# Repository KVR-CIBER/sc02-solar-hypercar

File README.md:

# SC-02 · Solar Hypercar

**Een gesloten Le-Mans-hypercar op zonne-energie, op schaal, voor de Solar Olympiade.**
De wagen is volledig 3D-printbaar (PLA + TPU-banden). Hij heeft een Raspberry Pi 4 en een ESP32-S3 aan boord, je bestuurt hem met een Bluetooth-controller of met je gsm, en alles is eerst in een fysica-simulatie getest voordat er één gram plastic geprint werd.

### ▶ [Website met films en beelden](https://kvr-ciber.github.io/sc02-solar-hypercar/) · 🏎 [Rij zelf in de simulatie](https://kvr-ciber.github.io/sc02-solar-hypercar/sim/) · 🔧 [3D-assemblage](https://kvr-ciber.github.io/sc02-solar-hypercar/sim/build.html)

|  |  |  |
|:---:|:---:|:---:|
| ▶ Rondje op het circuit | ▶ Assemblage | ▶ SC-01 Challenger |

## Specificaties

| | |
|---|---|
| Gewicht | ± 715 g (met 3S LiPo en Pi 4) |
| Batterij | 3S LiPo 1300 mAh (11,1 V) |
| Elektronica | Raspberry Pi 4 (brug naar controller/gsm) + ESP32-S3 (realtime aansturing) |
| Motordrivers | 2× DRV8871 (vooruit, achteruit, remmen) |
| Motoren | 2× Tamiya Hyper-Dash / Mach-Dash, of goedkope 130-motoren |
| Overbrenging | tandwielen module 0,8, 10:35. Printbaar, of CNC-gefreesd in POM |
| Zonnepaneel | 1 W, 110 × 60 mm, dwars op het dek |
| Banden | geprint in TPU 95A, klikken op de velg zoals een fietsband |
| Topsnelheid (simulatie) | ± 45 km/h met de Tamiya-motoren |

## Wat zit waar

| Map | Inhoud |
|---|---|
| [`f1/cad/`](f1/cad/) | Parametrische CadQuery-CAD: `p.py` (alle maten), `body.py` (carrosserie), `car.py` (alle onderdelen), `gears.py` (tandwielen), `build.py` (STL, STEP, DXF, GLB + controles) |
| [`f1/firmware/sc02/`](f1/firmware/sc02/) | ESP32-S3-firmware: motoren, stuurservo, tractiecontrole, failsafe, launch |
| [`f1/pi/`](f1/pi/) | Raspberry Pi 4: Bluetooth-controller + gsm-besturing via hotspot (`sc02_pi.py`, `phone.html`, systemd-service) |
| [`f1/web/`](f1/web/) | De 3D-simulatie in de browser (three.js) |
| [`PRINTEN_PLA_TPU/`](PRINTEN_PLA_TPU/) | **Alles printklaar**, al in de juiste printstand, met instructies |
| [`site/`](site/) | De projectwebsite (GitHub Pages), samengesteld door `site/build_site.sh` |
| [`video/`](video/) | Films in 1080p |
| [`docs/`](docs/) | Bedrading, stuklijst, ontwerpverslag, motormetingen, en het [README van de eerste versie (SC-01)](docs/SC-01_README.md) |
| `sim/`, `cad/`, `firmware/`, `pit/` | De eerste wagen SC-01 (Challenger-klasse) |

## Printen

Alles in **PLA**, alleen de **banden in TPU 95A**. Elk bestand staat al in de juiste printstand, en het getal vooraan de bestandsnaam (`2x_…`) zegt hoeveel je er nodig hebt.
De volledige instellingen per onderdeel staan in [`PRINTEN_PLA_TPU/LEESMIJ.md`](PRINTEN_PLA_TPU/LEESMIJ.md).

Kort:
- Carrosserie: 0,2 mm, tree supports, 3 wanden, 12 % infill.
- Velgen en tandwielen: 0,12 mm, 3 wanden, 25 % infill.
- Motorwieg en motorklem: liever 100 % infill, want de motoren worden warm.
- Banden: TPU, langzaam (± 25 mm/s), geen supports.

## Simulatie

Online speelbaar op **https://kvr-ciber.github.io/sc02-solar-hypercar/sim/** (WASD of pijltjes, spatie = rem, C = camera, R = reset, gamepad werkt ook). In de instellingen kies je tussen het **circuit** en een **oneindige rechte lijn** met afstandsteller en 12 m-sprinttimer. Met de knop **direct / BT · 35 ms / gsm · 120 ms** voel je de vertraging (met schommeling) die je zou hebben als je de echte wagen via de Pi bestuurt: Bluetooth-controller → Pi 4 → UART → ESP32, of gsm via de hotspot. Dat zijn schattingen, nog niet gemeten op de echte wagen.

Lokaal draaien:

```bash
cd f1/web
python3 -m http.server 8000
# open http://localhost:8000
```

## Hoe we het gemaakt hebben

1. **Reglement eerst.** We begonnen met het reglement van de Solar Olympiade: maximale breedte, verplicht zonnepaneel met diode, batterijregels. Elke ontwerpkeuze moest daar binnen passen.

2. **Fysica-simulatie (SC-01).** Voor de eerste wagen schreven we een race-simulatie met batterij, motor, bandslip en launch control. Daarmee kozen we motor, overbrenging en wielmaat. Resultaat: **2,33 s over 12 m** vanuit stilstand. Zie [docs/SC-01_README.md](docs/SC-01_README.md).

3. **Parametrische CAD.** Het hele model is code (CadQuery). Eén maat aanpassen in `p.py`, `build.py` draaien, en alle STL-, STEP- en DXF-bestanden worden opnieuw gemaakt.

4. **"Te speelgoed."** De eerste versie werkte, maar zag eruit als speelgoed: open wielen, zichtbare draden en schroeven. Dat was de belangrijkste feedback.

5. **SC-02: gesloten Le-Mans-hypercar.** Daarom een volledig nieuw ontwerp: wielen in wielkasten, een gesloten carrosserie, een koepel, achtervleugel, splitter en diffuser. Van buiten zie je niets van de techniek.

6. **CAD-problemen opgelost.** Een paar die we onderweg tegenkwamen:
   - **OCC-booleans faalden stil.** Ze gaven een leeg of kapot resultaat zonder foutmelding. Oplossing: de booleans laten doen door `manifold3d`, dat altijd een waterdicht resultaat geeft.
   - **De loft vouwde de staart en de neus terug.** De carrosserie klapte op zichzelf. Oplossing: rechtstreeks OCC `ThruSections` aanroepen, met volledige controle over de doorsneden.
   - **Zwevende magneetbosjes.** De houders voor de magneten van de carrosserie hingen in de lucht, los van de wand. Ze zijn nu verbonden met de structuur.
   - **Botsende onderdelen.** Een volledige botsingscontrole test elk onderdeel tegen elk ander (nu: 0 botsingen). Zo vonden we o.a. een diffuser in de vloer, splitter-vinnen door de vloer, een koepel door het dek, een te korte batterijbak en ESP-pinnen door de Pi-USB.
   - **Twee echte ontwerpfouten.** De carrosserie zat vast op de achteras (gesloten wielkasten): nu zijn de asgleuf en wielkasten onderaan open en tilt de body er gewoon af. En de motoren konden niet in het tandwiel zakken: nu schuiven ze langs hun as van achteren in de wieg.

7. **Firmware en Pi-brug.** De ESP32-S3 doet het realtime werk: tractiecontrole, een failsafe die stopt als het signaal wegvalt, en een launch-modus. De Pi 4 is de brug: hij leest een Bluetooth-controller in, en via een hotspot kun je ook met je gsm sturen.

8. **three.js-simulatie.** Een 3D-simulatie in de browser met een fietsmodel voor het sturen, Pacejka-banden voor de grip, en het verbruik per onderdeel (Pi, ESP, servo, motoren), live tijdens het rijden.

9. **Printplaten en STEP-bestanden.** Alle onderdelen zijn verdeeld over printplaten, in de juiste printstand, en ook beschikbaar als STEP om verder te bewerken in Fusion, FreeCAD of Onshape.

10. **Budget.** We vergeleken AliExpress met Europese leveranciers, inclusief de EU-invoerheffing op kleine pakketjes. Goedkoop bestellen is niet altijd goedkoper.

11. **Assemblage-animatie.** 24 stappen, en elke montagebeweging is nagerekend tegen de CAD (40 punten per baan): geen enkel onderdeel gaat door een ander. Ook [interactief in 3D](https://kvr-ciber.github.io/sc02-solar-hypercar/sim/build.html).

## Niet in deze repo

- Het reglement van de Solar Olympiade (auteursrecht van de organisatie).
- Wachtwoorden: kopieer `firmware/solar_car/secrets.example.h` naar `secrets.h` en vul je eigen hotspotgegevens in.
- 4K-video's (te groot voor GitHub; de 1080p-versies staan erin).

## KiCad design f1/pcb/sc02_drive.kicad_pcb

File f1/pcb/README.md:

# SC-02 drive board (v3.0)

A **compact 86 x 90 mm board on 4x M3 standoffs**, with the 3S LiPo on top of it. No Raspberry Pi anymore, a **built-in
ExpressLRS 2.4 GHz receiver** for the RadioMaster Pocket, and a real **solar-panel connector**.
(v2 was the whole car floor; that is gone: the car floor goes back to the 2 mm acrylic / printed floor.)

| Block | Parts |
|---|---|
| Power (unchanged from v2) | **XT60**, 10 A fuse, power switch pads, P-MOSFET reverse protection, **INA226** + 2 mOhm shunt, **TPS54560B 5 V 5 A** buck |
| Car brain | **ESP32-S3-WROOM-1** (antenna at the bottom edge), USB-C at the edge, RESET / BOOT |
| Motor | **one brushless 2435 4500 KV + 40 A ESC** (11:35). The ESC takes its power straight from the battery (Y-cable on the XT60); this board only sends the throttle signal (**ESC** header, IO4) and reads a 10k NTC on the ESC/motor (**ESC TEMP**, IO5) for the boost limit |
| **ExpressLRS receiver** | **ESP32-C3-MINI-1** + **Ebyte E28-2G4M12S** (SX1280, 12.5 dBm, PCB antenna at the right edge), own 3.3 V LDO, RGB status LED, BIND button |
| Connectors | servo (MG90S), hall (A3144), lights (switched 5 V), **solar panel JST-XH 2-pin**, Qwiic I2C |

Checks: **DRC 0, unconnected 0, ERC 0, schematic parity 0.** JLC BOM/CPL in `fab/` with LCSC numbers.

## ExpressLRS: flashing and binding
The receiver is wired exactly like ExpressLRS' **"Generic C3 2400"** target (SCK 6, MOSI 4, MISO 5, NSS 7, BUSY 3, DIO1 1,
RST 2, LED 8, button 9, CRSF on 20/21), so the normal ExpressLRS firmware runs on it, no custom layout needed.
1. First flash: ExpressLRS Configurator -> target **Generic C3 2400 RX**, flash method **WiFi** or via the **RX USB** pads
   (D-, D+, GND: a cut USB cable) while holding **BIND** at power-on.
2. Bind with the Pocket (binding phrase, or press BIND 3x).
3. CRSF goes to the car ESP32-S3: C3 TX -> **IO16**, S3 **IO15** -> C3 RX (420000 baud). The S3 can reset the receiver
   (**IO17** -> EN) and start its bootloader (**IO18** -> IO9), so later updates can go through the car's USB-C.
Tip: keep the S3's own WiFi off while driving (same 2.4 GHz band).

## Solar panel
JST-XH 2-pin (**-** / **+**), voltage on IO8 (x 4.03). Solder jumper **JP1 (ZON>5V)**, open by default: closed, the panel
helps the 5 V rail through a Schottky diode. Only close it with a panel whose open-circuit voltage is at most 6 V.

## ESP32-S3 pins
| GPIO | | GPIO | |
|---|---|---|---|
| 4 | ESC throttle (servo PWM / DShot) | 5 | ESC/motor NTC (ADC) |
| 9 | servo | 38 | hall |
| 15 / 16 | CRSF TX / RX (receiver) | 17 / 18 | receiver EN / BOOT |
| 1 / 2 | I2C SDA / SCL (INA226 0x40 + Qwiic) | 8 | solar panel voltage |
| 11 | lights | 12 | yellow LED |

## Still to do
* Car CAD: floor back to acrylic + 4 standoff holes for this board, battery tray on top, USB-C opening at the new place.
* Firmware `car.cpp`: ESC on IO4 (with arming), CRSF on IO15/16, boost on CH5 with the NTC temperature limit, hall IO38.
* ESC wiring: XT60 Y-cable battery -> ESC + this board; do NOT connect the ESC's red BEC wire to the board.

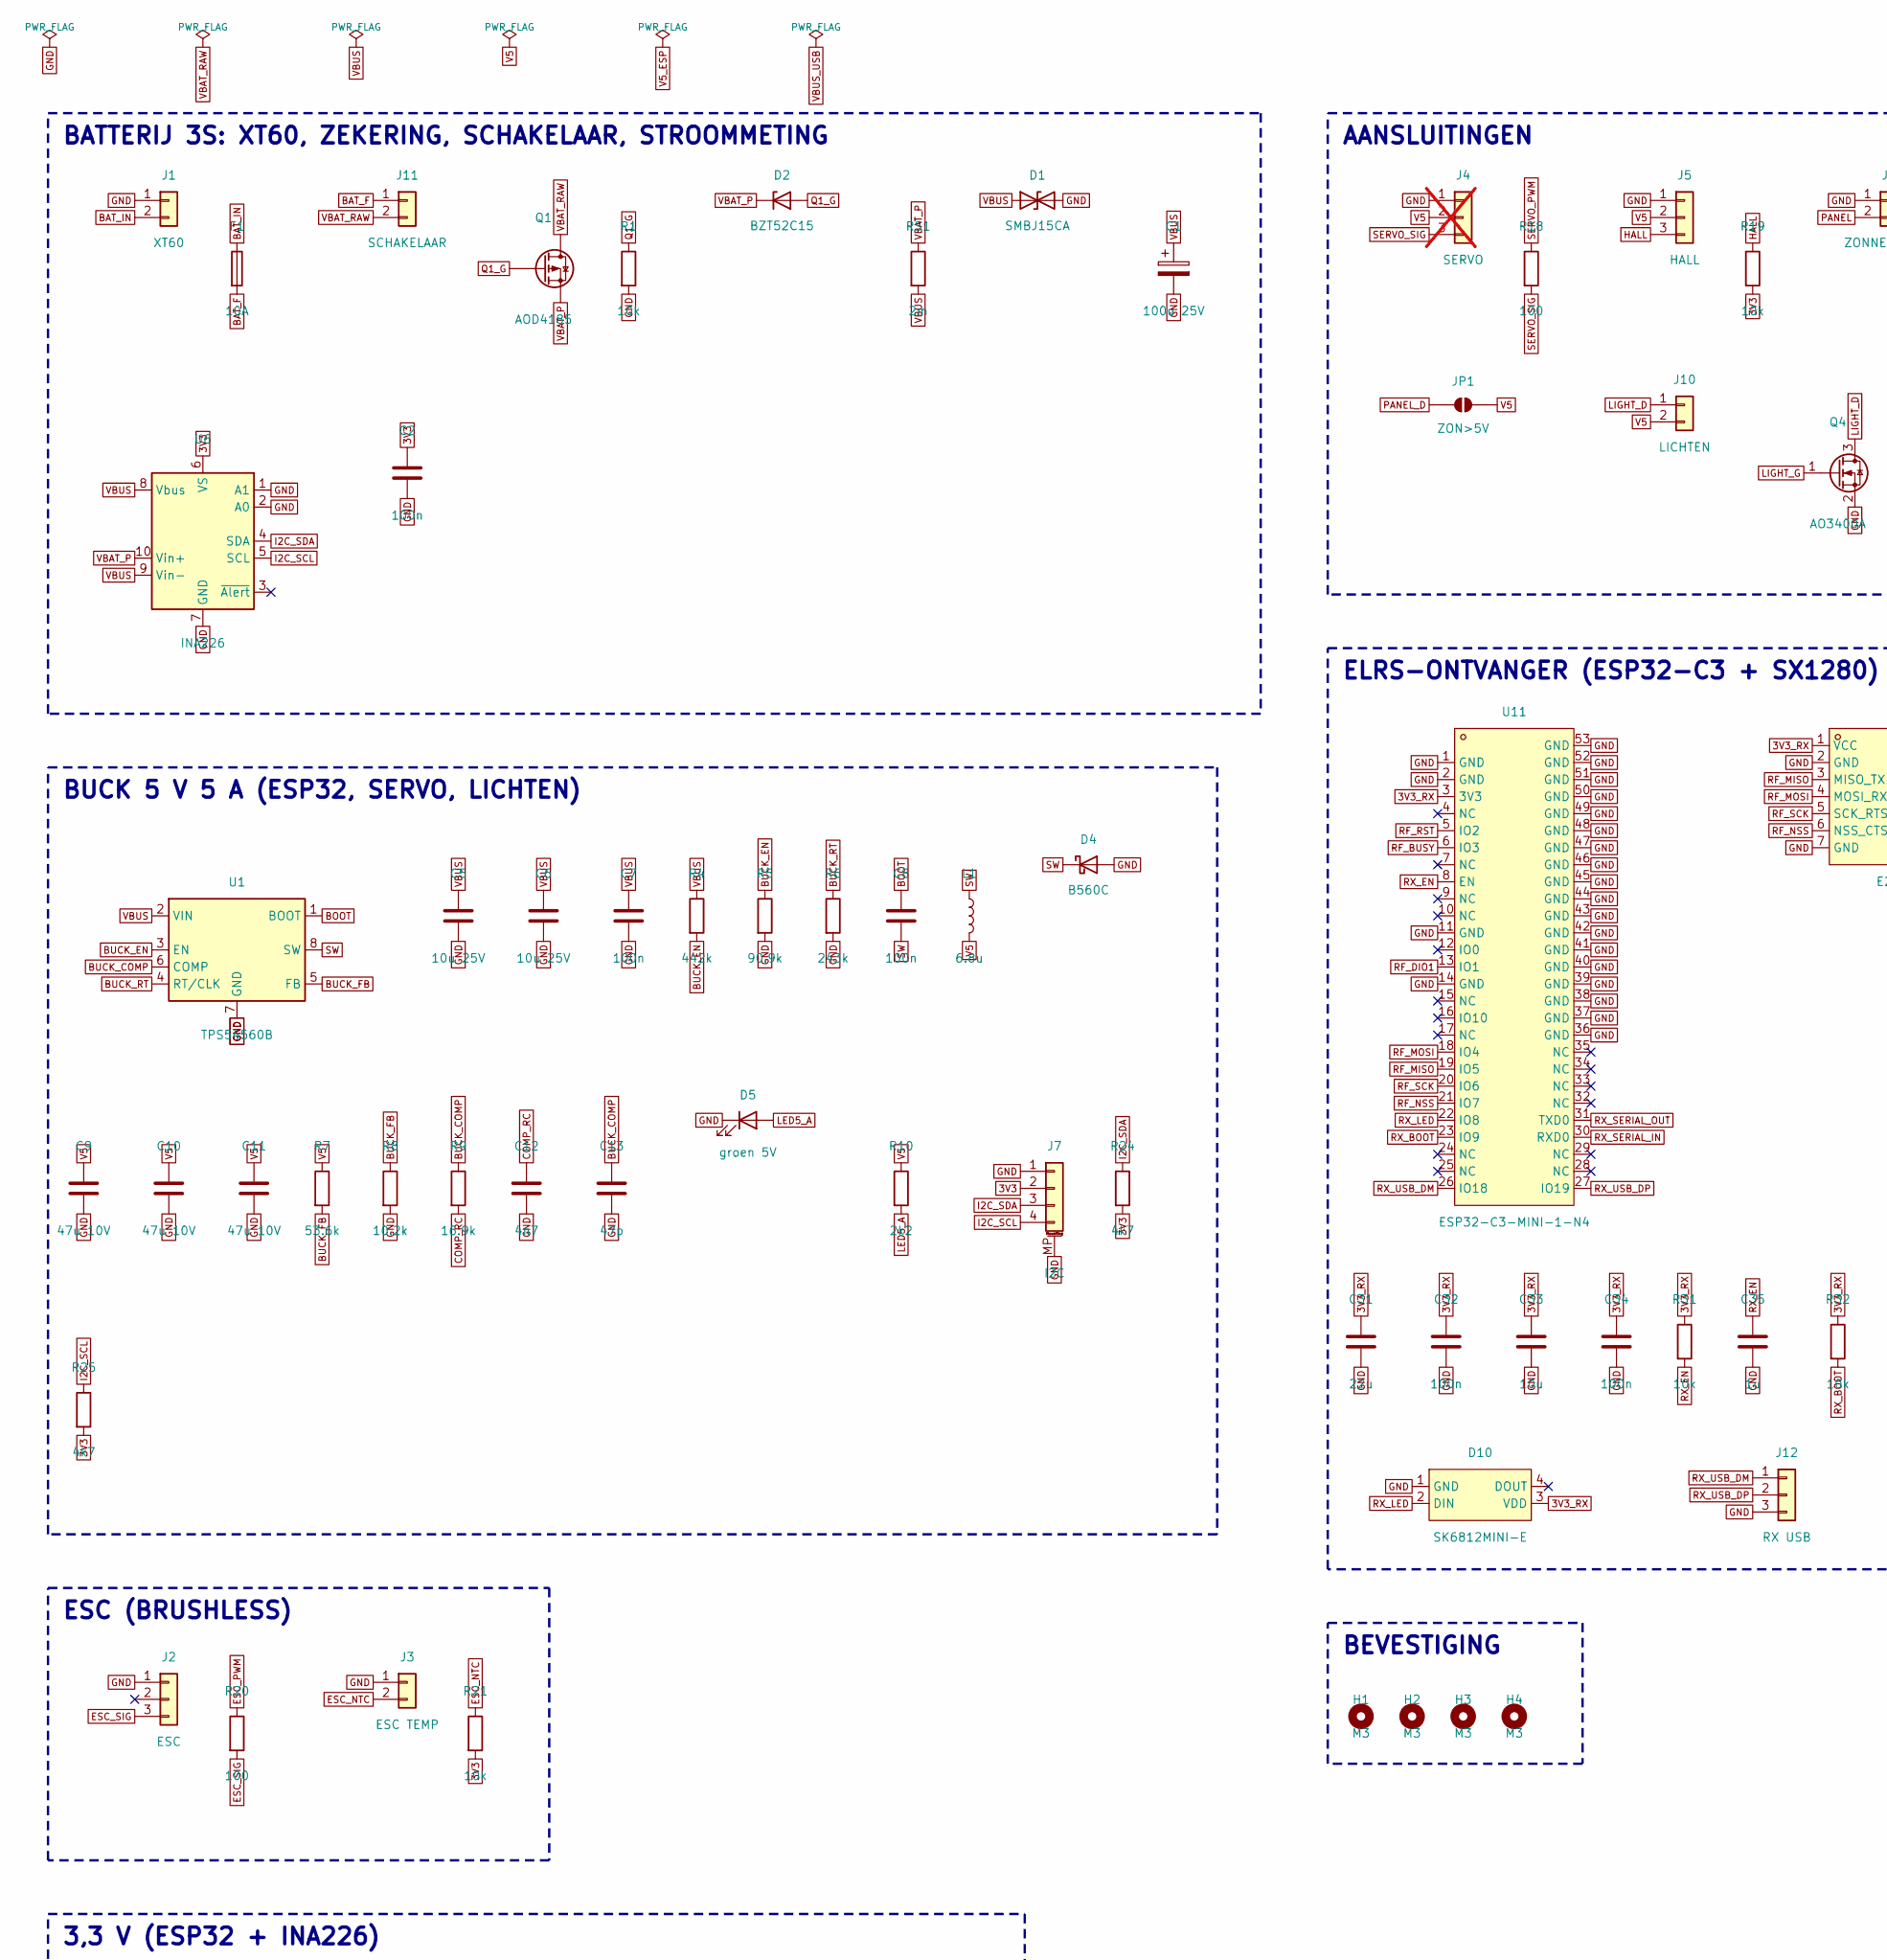
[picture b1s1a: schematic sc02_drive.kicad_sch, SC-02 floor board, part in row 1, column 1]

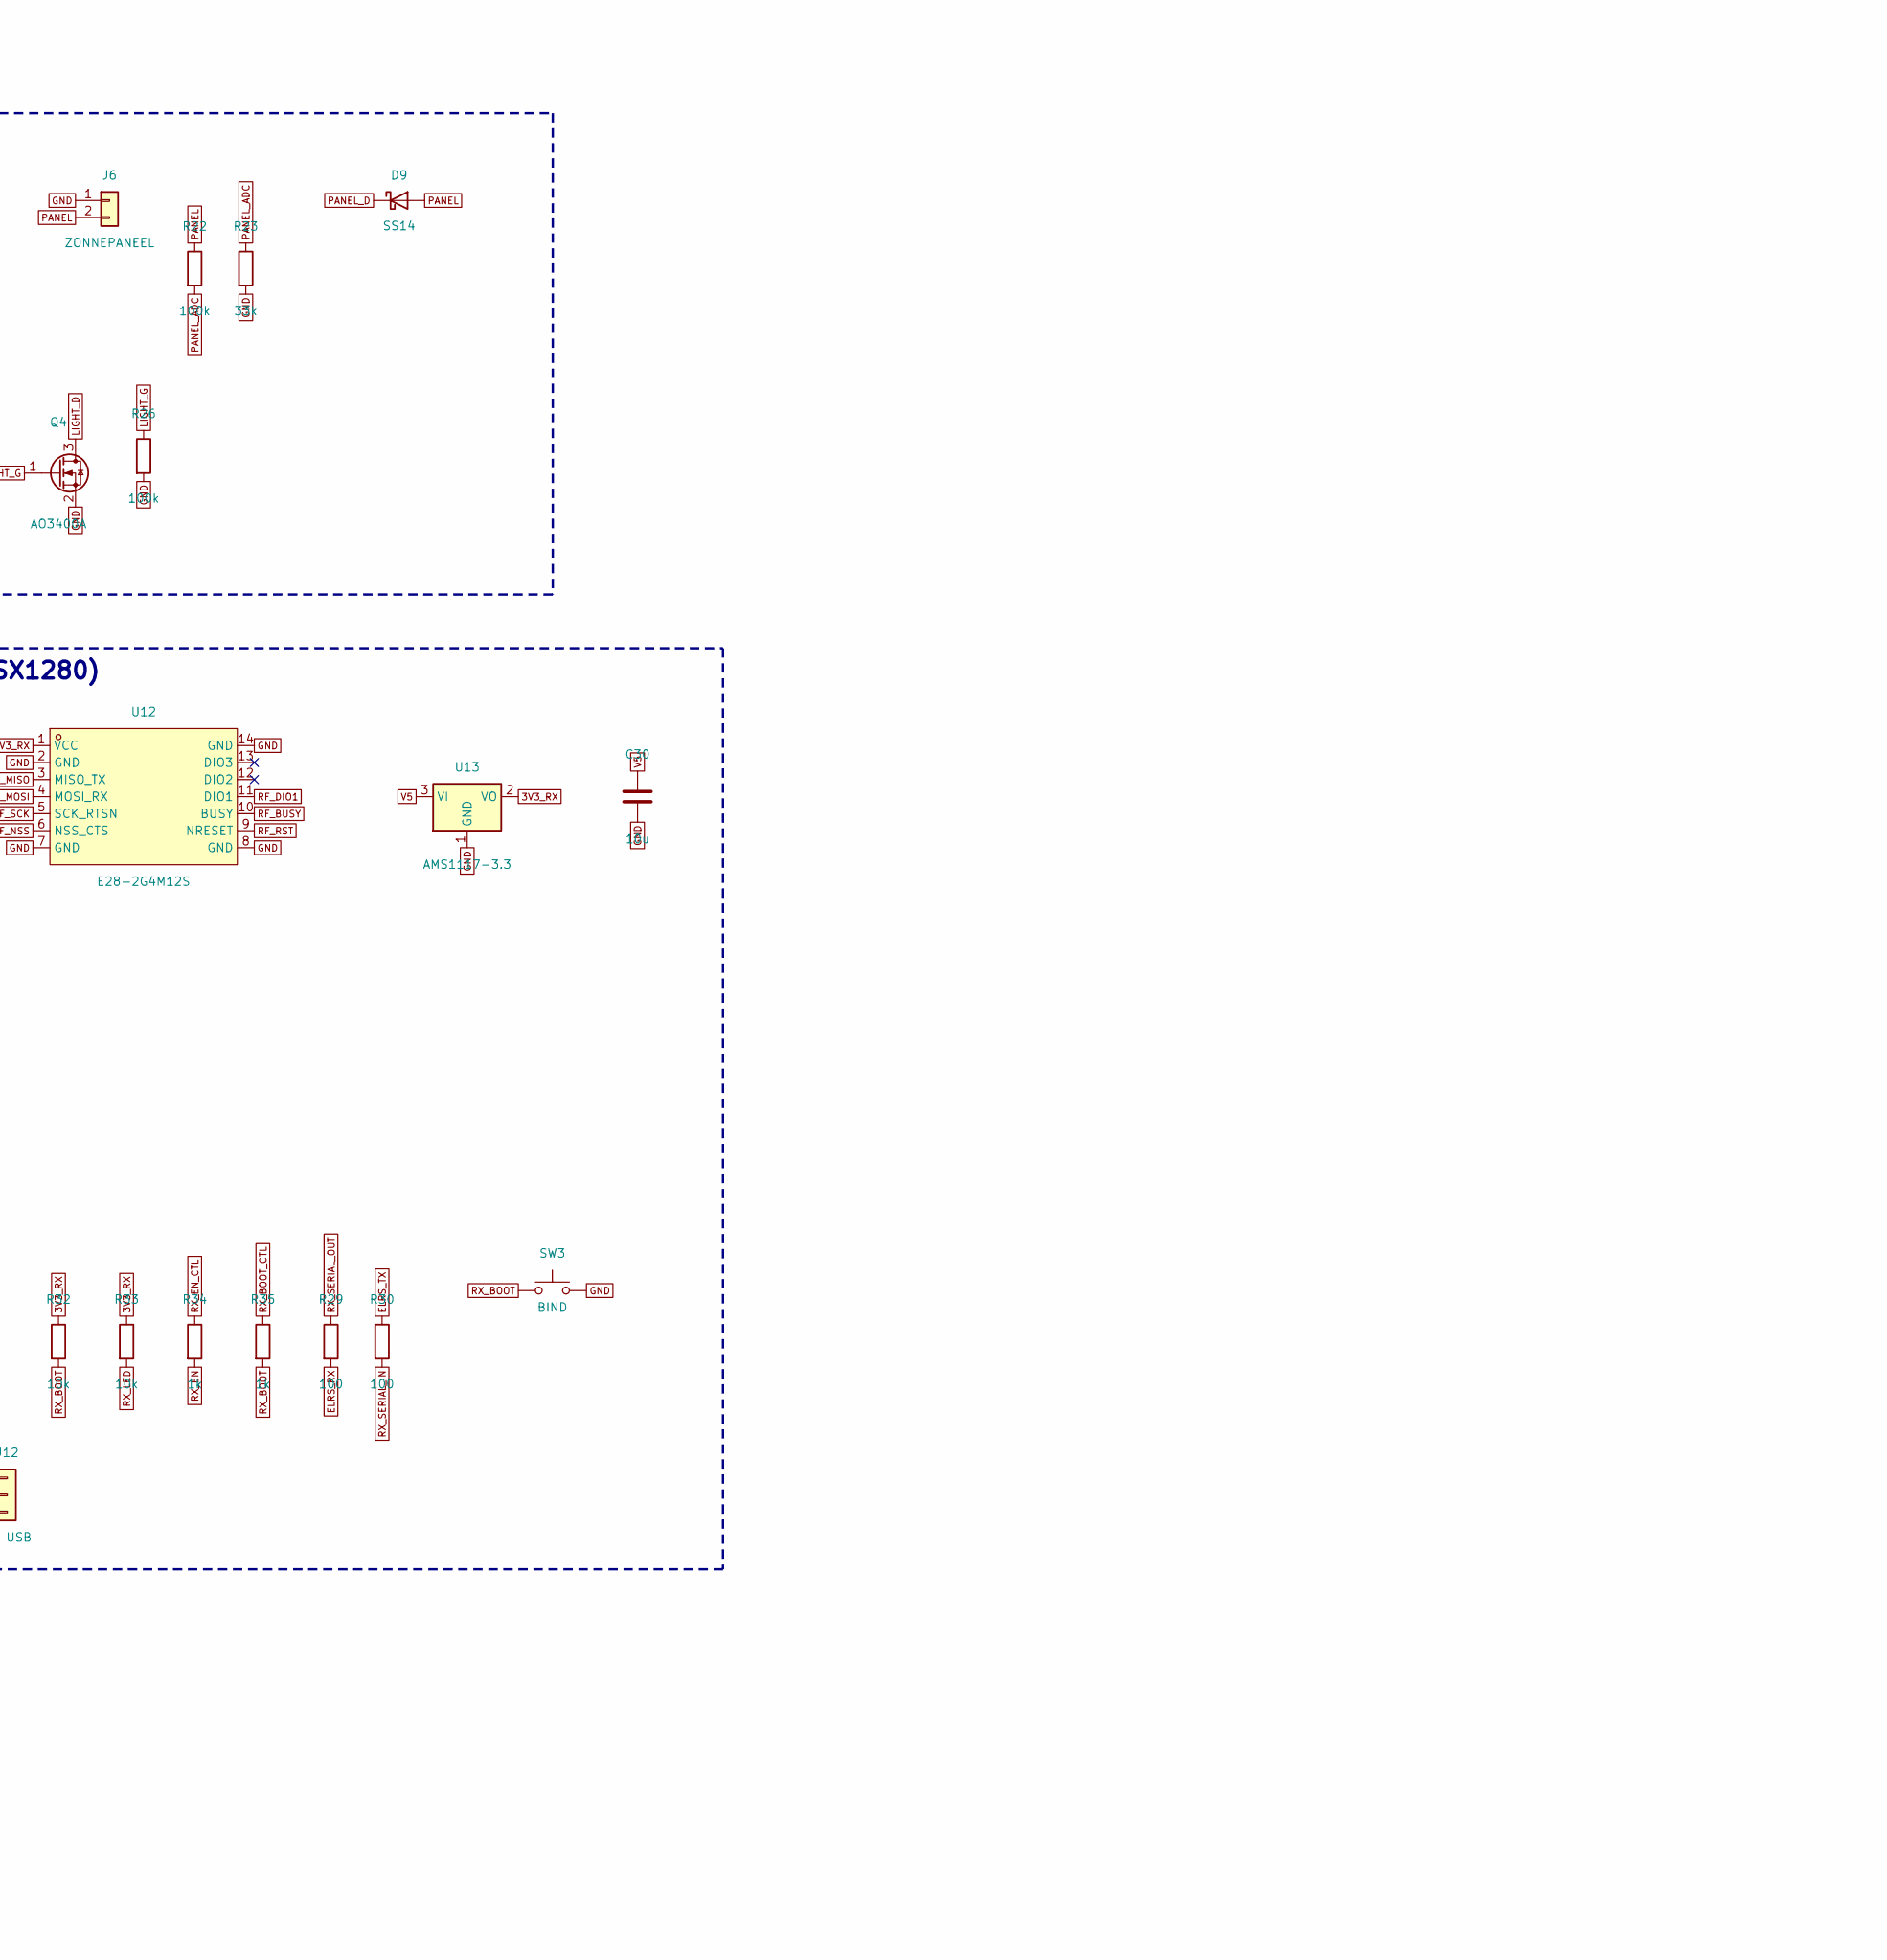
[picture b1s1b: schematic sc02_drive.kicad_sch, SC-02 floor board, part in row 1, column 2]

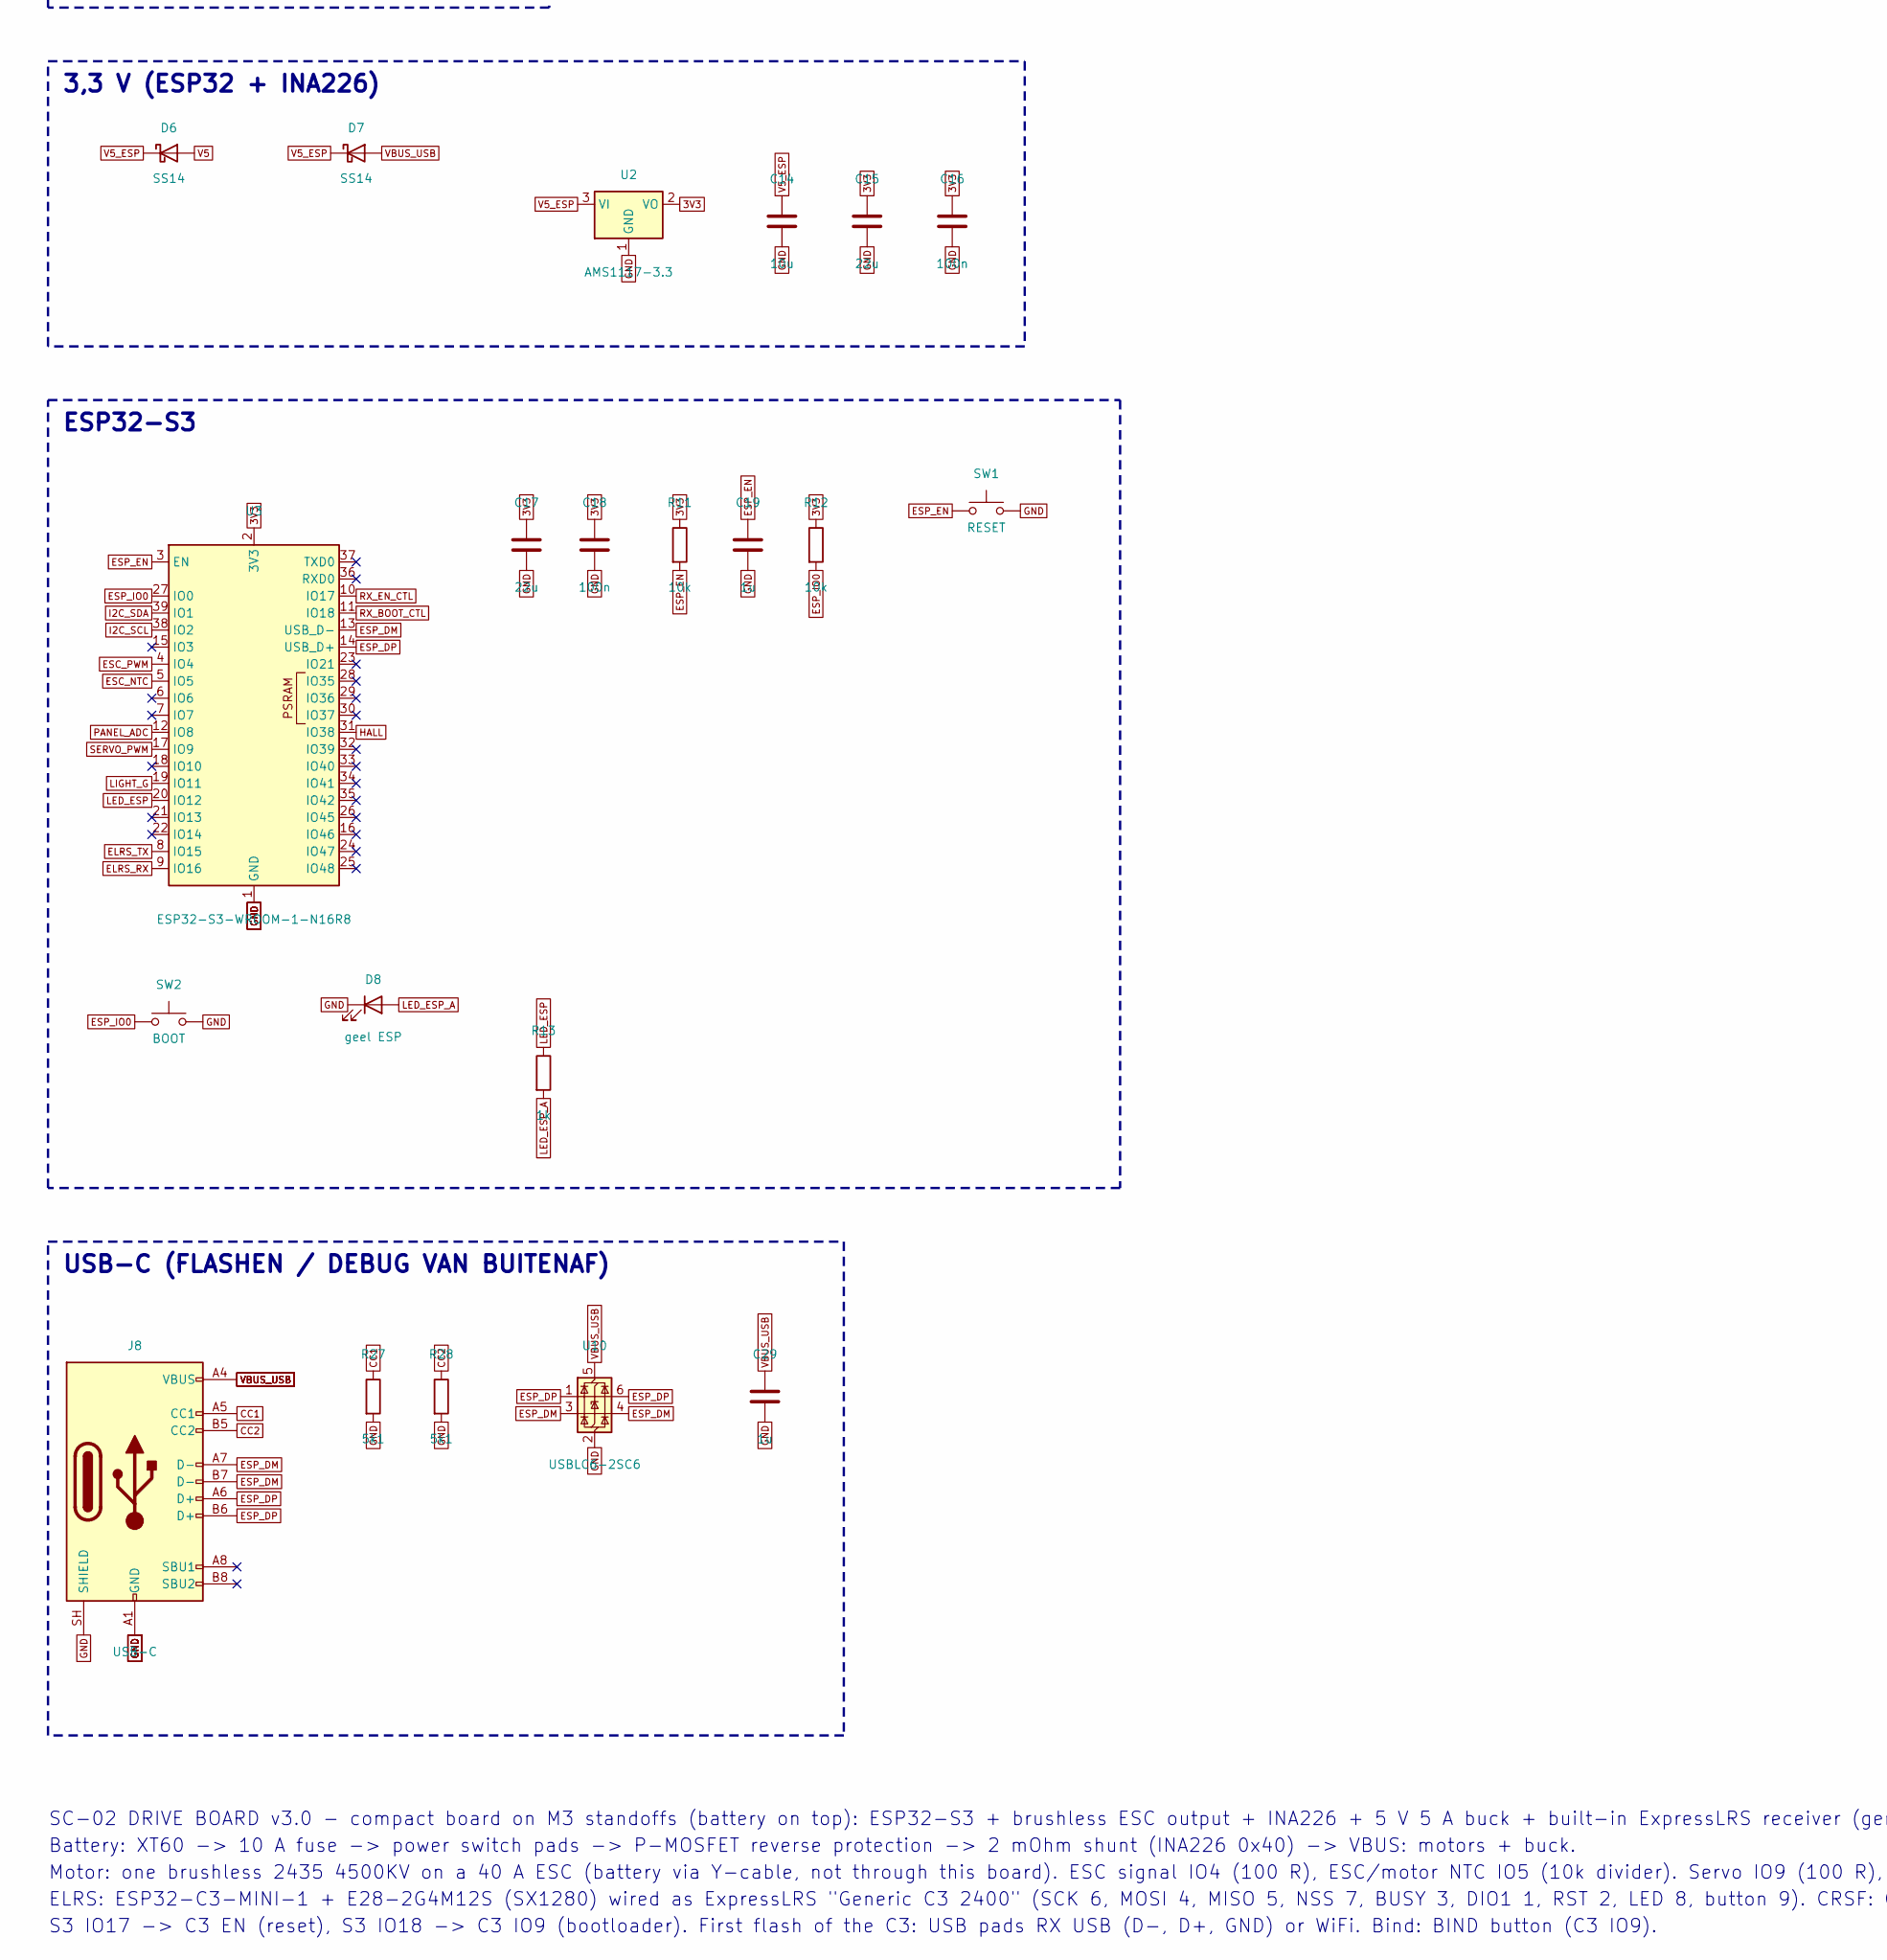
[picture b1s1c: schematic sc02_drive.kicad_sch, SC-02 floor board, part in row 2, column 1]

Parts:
C1: 100u 25V; CP_Elec_6.3x7.7; MPN 100uF 25V 6.3x7.7 alu
C2, C7, C8, C16, C18, C32, C34: 100n; C_0603_1608Metric; MPN 0603 100n X7R ceramic
C5, C6: 10u 25V; C_1206_3216Metric; MPN 1206 10u 25V X5R ceramic
C9, C10, C11: 47u 10V; C_1210_3225Metric; MPN 1210 47u 10V X5R ceramic
C12: 4n7; C_0603_1608Metric; MPN 0603 4n7 X5R ceramic
C13: 47p; C_0603_1608Metric; MPN 0603 47p X7R ceramic
C14, C30, C33: 10u; C_0805_2012Metric; MPN 0805 10u X5R ceramic
C15, C17, C31: 22u; C_0805_2012Metric; MPN 0805 22u X5R ceramic
C19, C29, C35: 1u; C_0603_1608Metric; MPN 0603 1u X5R ceramic
D1: SMBJ15CA; D_SMB; MPN SMBJ15CA
D2: BZT52C15; D_SOD-123; MPN BZT52C15 (gate clamp)
D4: B560C; D_SMC; MPN B560C (5 A 60 V Schottky)
D5: groen 5V; LED_0603_1608Metric; MPN LED 0603 green
D6, D7: SS14; D_SMA; MPN SS14
D8: geel ESP; LED_0603_1608Metric; MPN LED 0603 yellow
D9: SS14; D_SMA; MPN SS14 (solar -> 5 V)
D10: SK6812MINI-E; LED-SMD_4P-L3.2-W2.8-LS5.9_SK6812MINI-E; MPN SK6812MINI-E (ELRS status LED, RGB)
F1: 10A; R_2512_6332Metric; MPN 2410FA-10A (fast 10 A, 2410 body on 251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
H1, H2, H3, H4: M3; Hole_3.2mm
J1: XT60; AMASS_XT60-M_1x02_P7.20mm_Vertical; MPN AMASS XT60-M (male, vertical): the LiPo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
J2: ESC; PinHeader_1x03_P2.54mm_Vertical; MPN 1x3 pin header 2.54 (ESC signal lead: b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
J3: ESC TEMP; SolderWire_2pad_P5mm_M; MPN solder pads: 10k NTC glued on the ESC /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
J4: SERVO; PinHeader_1x03_P2.54mm_Vertical; MPN NOT FITTED: solder the MG90S lead strai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; not fitted
J5: HALL; PinHeader_1x03_P2.54mm_Vertical; MPN 1x3 pin header 2.54 (A3144: GND, 5 V, o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
J6: ZONNEPANEEL; JST_XH_B2B-XH-A_1x02_P2.50mm_Vertical; MPN JST XH 2-pin (B2B-XH-A): plug the solar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
J7: I2C; JST_SH_SM04B-SRSS-TB_1x04-1MP_P1.00mm_Horizontal; MPN JST SM04B-SRSS-TB (Qwiic / STEMMA QT)
J8: USB-C; USB_C_Receptacle_HRO_TYPE-C-31-M-12; MPN HRO TYPE-C-31-M-12 (board edge)
J10: LICHTEN; SolderWire_2pad_P4mm_S; MPN solder pads, LED lights 5 V (with their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
J11: SCHAKELAAR; SolderWire_2pad_P5mm_SW; MPN solder pads for the power switch (mount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
J12: RX USB; Pads_RX_USB; MPN test pads: USB D-/D+/GND of the receive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
JP1: ZON>5V; SolderJumper-2_P1.3mm_Open_RoundedPad1.0x1.5mm; MPN solder jumper (open): solar panel feeds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
L1: 6.8u; L_Bourns_SRP1038C_10.0x10.0mm; MPN Bourns SRP1038C-6R8M (6.8 uH, >= 8 A)
Q1: AOD4185; TO-252-2; MPN AOD4185 (P-MOSFET 40 V 40 A, reverse po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
Q4: AO3400A; SOT-23; MPN AO3400A
R1, R11, R12, R19, R31, R32: 10k; R_0603_1608Metric; MPN 0603 10k 1%
R4: 442k; R_0603_1608Metric; MPN 0603 442k 1%
R5: 90.9k; R_0603_1608Metric; MPN 0603 90.9k 1%
R6: 243k; R_0603_1608Metric; MPN 0603 243k 1%
R7: 53.6k; R_0603_1608Metric; MPN 0603 53.6k 1%
R8: 10.2k; R_0603_1608Metric; MPN 0603 10.2k 1%
R9: 16.9k; R_0603_1608Metric; MPN 0603 16.9k 1%
R10: 2k2; R_0603_1608Metric; MPN 0603 2k2 1%
R13: 1k; R_0603_1608Metric; MPN 0603 1k 1%
R18, R20, R29, R30: 100; R_0603_1608Metric; MPN 0603 100 1%
R21: 10k; R_0603_1608Metric; MPN 0603 10k 1% (NTC divider)
R22, R26: 100k; R_0603_1608Metric; MPN 0603 100k 1%
R23: 33k; R_0603_1608Metric; MPN 0603 33k 1%
R24, R25: 4k7; R_0603_1608Metric; MPN 0603 4k7 1%
R27, R28: 5k1; R_0603_1608Metric; MPN 0603 5k1 1%
R33: 10k; R_0603_1608Metric; MPN 0603 10k (IO8 strapping pin high at boo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
R34: 1k; R_0603_1608Metric; MPN 0603 1k (S3 can reset the receiver)
R35: 1k; R_0603_1608Metric; MPN 0603 1k (S3 can start the receiver boot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
RS1: 2m; R_2512_6332Metric; MPN 2512 2 mOhm 2 W current shunt
SW1: RESET; SW_Push_1P1T_NO_CK_KMR2; MPN CK KMR221G (4.2x2.8 tact)
SW2: BOOT; SW_Push_1P1T_NO_CK_KMR2; MPN CK KMR221G (4.2x2.8 tact) - also the ra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
SW3: BIND; SW_Push_1P1T_NO_CK_KMR2; MPN CK KMR221G: ELRS bind / bootloader butt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
U1: TPS54560B; Texas_R-PDSO-G8_EP2.95x4.9mm_Mask2.4x3.1mm_ThermalVias; MPN TPS54560BDDAR
U2: AMS1117-3.3; SOT-223-3_TabPin2; MPN AMS1117-3.3
U3: ESP32-S3-WROOM-1-N16R8; ESP32-S3-WROOM-1; MPN ESP32-S3-WROOM-1-N16R8
U6: INA226; TSSOP-10_3x3mm_P0.5mm; MPN INA226AIDGSR (0x40)
U10: USBLC6-2SC6; SOT-23-6; MPN USBLC6-2SC6
U11: ESP32-C3-MINI-1-N4; WIFIM-SMD_ESP32-C3-MINI-1; MPN ESP32-C3-MINI-1-N4 (ELRS receiver MCU, 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
U12: E28-2G4M12S; WIRELM-SMD_E28-2G4M12S; MPN Ebyte E28-2G4M12S (SX1280 2.4 GHz, 12.5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
U13: AMS1117-3.3; SOT-223-3_TabPin2; MPN AMS1117-3.3 (receiver supply)

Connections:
3V3: C2.1, C15.1, C16.1, C17.1, C18.1, J7.2, R11.1, R12.1, R19.2, R21.2, R24.2, R25.2, U2.2 (VO), U3.2 (3V3), U6.6 (VS)
3V3_RX: C31.1, C32.1, C33.1, C34.1, D10.3 (VDD), R31.1, R32.1, R33.1, U11.3 (3V3), U12.1 (VCC), U13.2 (VO)
BAT_F: F1.2, J11.1
BAT_IN: F1.1, J1.2
BOOT: C8.1, U1.1 (BOOT)
BUCK_COMP: C13.1, R9.1, U1.6 (COMP)
BUCK_EN: R4.2, R5.1, U1.3 (EN)
BUCK_FB: R7.2, R8.1, U1.5 (FB)
BUCK_RT: R6.1, U1.4 (RT/CLK)
CC1: J8.A5 (CC1), R27.1
CC2: J8.B5 (CC2), R28.1
COMP_RC: C12.1, R9.2
ELRS_RX: R29.2, U3.9 (IO16)
ELRS_TX: R30.1, U3.8 (IO15)
ESC_NTC: J3.2, R21.1, U3.5 (IO5)
ESC_PWM: R20.1, U3.4 (IO4)
ESC_SIG: J2.3, R20.2
ESP_DM: J8.A7 (D-), J8.B7 (D-), U3.13 (USB_D-), U10.3 (I/O2), U10.4 (I/O2)
ESP_DP: J8.A6 (D+), J8.B6 (D+), U3.14 (USB_D+), U10.1 (I/O1), U10.6 (I/O1)
ESP_EN: C19.1, R11.2, SW1.1, U3.3 (EN)
ESP_IO0: R12.2, SW2.1, U3.27 (IO0)
GND: C1.2, C2.2, C5.2, C6.2, C7.2, C9.2, C10.2, C11.2, C12.2, C13.2, C14.2, C15.2, C16.2, C17.2, C18.2, C19.2, C29.2, C30.2, C31.2, C32.2, C33.2, C34.2, C35.2, D1.2 (A2), D4.2 (A), D5.1 (K), D8.1 (K), D10.1 (GND), J1.1, J2.1, J3.1, J4.1, J5.1, J6.1, J7.1, J7.MP (MountPin), J8.A1 (GND), J8.A12 (GND), J8.B1 (GND), J8.B12 (GND), J8.SH (SHIELD), J12.3, Q4.2 (S), R1.2, R5.2, R6.2, R8.2, R23.2, R26.2, R27.2, R28.2, SW1.2, SW2.2, SW3.2, U1.7 (GND), U1.9 (GND), U2.1 (GND), U3.1 (GND), U3.40 (GND), U3.41 (GND), U6.1 (A1), U6.2 (A0), U6.7 (GND), U10.2 (GND), U11.1 (GND), U11.2 (GND), U11.11 (GND), U11.14 (GND), U11.36 (GND), U11.37 (GND), U11.38 (GND), U11.39 (GND), U11.40 (GND), U11.41 (GND), U11.42 (GND), U11.43 (GND), U11.44 (GND), U11.45 (GND), U11.46 (GND), U11.47 (GND), U11.48 (GND), U11.49 (GND), U11.50 (GND), U11.51 (GND), U11.52 (GND), U11.53 (GND), U12.2 (GND), U12.7 (GND), U12.8 (GND), U12.14 (GND), U13.1 (GND)
HALL: J5.3, R19.1, U3.31 (IO38)
I2C_SCL: J7.4, R25.1, U3.38 (IO2), U6.5 (SCL)
I2C_SDA: J7.3, R24.1, U3.39 (IO1), U6.4 (SDA)
LED5_A: D5.2 (A), R10.2
LED_ESP: R13.1, U3.20 (IO12)
LED_ESP_A: D8.2 (A), R13.2
LIGHT_D: J10.1, Q4.3 (D)
LIGHT_G: Q4.1 (G), R26.1, U3.19 (IO11)
PANEL: D9.2 (A), J6.2, R22.1
PANEL_ADC: R22.2, R23.1, U3.12 (IO8)
PANEL_D: D9.1 (K), JP1.1 (A)
Q1_G: D2.2 (A), Q1.1 (G), R1.1
RF_BUSY: U11.6 (IO3), U12.10 (BUSY)
RF_DIO1: U11.13 (IO1), U12.11 (DIO1)
RF_MISO: U11.19 (IO5), U12.3 (MISO_TX)
RF_MOSI: U11.18 (IO4), U12.4 (MOSI_RX)
RF_NSS: U11.21 (IO7), U12.6 (NSS_CTS)
RF_RST: U11.5 (IO2), U12.9 (NRESET)
RF_SCK: U11.20 (IO6), U12.5 (SCK_RTSN)
RX_BOOT: R32.2, R35.2, SW3.1, U11.23 (IO9)
RX_BOOT_CTL: R35.1, U3.11 (IO18)
RX_EN: C35.1, R31.2, R34.2, U11.8 (EN)
RX_EN_CTL: R34.1, U3.10 (IO17)
RX_LED: D10.2 (DIN), R33.2, U11.22 (IO8)
RX_SERIAL_IN: R30.2, U11.30 (RXD0)
RX_SERIAL_OUT: R29.1, U11.31 (TXD0)
RX_USB_DM: J12.1, U11.26 (IO18)
RX_USB_DP: J12.2, U11.27 (IO19)
SERVO_PWM: R18.1, U3.17 (IO9)
SERVO_SIG: J4.3, R18.2
SW: C8.2, D4.1 (K), L1.1, U1.8 (SW)
V5: C9.1, C10.1, C11.1, C30.1, D6.2 (A), J4.2, J5.2, J10.2, JP1.2 (B), L1.2, R7.1, R10.1, U13.3 (VI)
V5_ESP: C14.1, D6.1 (K), D7.1 (K), U2.3 (VI)
VBAT_P: D2.1 (K), Q1.3 (S), RS1.1, U6.10 (Vin+)
VBAT_RAW: J11.2, Q1.2 (D)
VBUS: C1.1, C5.1, C6.1, C7.1, D1.1 (A1), R4.1, RS1.2, U1.2 (VIN), U6.8 (Vbus), U6.9 (Vin-)
VBUS_USB: C29.1, D7.2 (A), J8.A4 (VBUS), J8.A9 (VBUS), J8.B4 (VBUS), J8.B9 (VBUS), U10.5 (VBUS)

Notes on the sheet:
BATTERIJ 3S: XT60, ZEKERING, SCHAKELAAR, STROOMMETING
BUCK 5 V 5 A (ESP32, SERVO, LICHTEN)
ESC (BRUSHLESS)
3,3 V (ESP32 + INA226)
ESP32-S3
USB-C (FLASHEN / DEBUG VAN BUITENAF)
AANSLUITINGEN
ELRS-ONTVANGER (ESP32-C3 + SX1280)
BEVESTIGING
SC-02 DRIVE BOARD v3.0 - compact board on M3 standoffs (battery on top): ESP32-S3 + brushless ESC output + INA226 + 5 V 5 A buck + built-in ExpressLRS receiver (generated by tools/build_sch.py from tools/design.py)
Battery: XT60 -> 10 A fuse -> power switch pads -> P-MOSFET reverse protection -> 2 mOhm shunt (INA226 0x40) -> VBUS: motors + buck.
Motor: one brushless 2435 4500KV on a 40 A ESC (battery via Y-cable, not through this board). ESC signal IO4 (100 R), ESC/motor NTC IO5 (10k divider). Servo IO9 (100 R), hall IO38 (10k pull-up), lights IO11 (AO3400A), solar panel JST-XH, ADC IO8 (100k/33k), JP1 = panel -> 5 V.
ELRS: ESP32-C3-MINI-1 + E28-2G4M12S (SX1280) wired as ExpressLRS "Generic C3 2400" (SCK 6, MOSI 4, MISO 5, NSS 7, BUSY 3, DIO1 1, RST 2, LED 8, button 9). CRSF: C3 TX21 -> S3 IO16, S3 IO15 -> C3 RX20.
S3 IO17 -> C3 EN (reset), S3 IO18 -> C3 IO9 (bootloader). First flash of the C3: USB pads RX USB (D-, D+, GND) or WiFi. Bind: BIND button (C3 IO9).
